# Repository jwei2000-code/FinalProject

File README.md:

# FinalProject
# The "Deep Work Halo"

## 1. Overview
The Deep Work Halo is a privacy-focused workspace monitor designed to help users maintain and signal a "Flow State" without distraction. It consists of a discreet wearable that analyzes head stability to detect focus levels and wirelessly updates a desktop analog gauge. This gauge visually communicates the user's cognitive state to colleagues, acting as an automatic "Do Not Disturb" signal when deep work is achieved.

## 2. Visual Concept & Physical Design

### The Sensing Device (The "Smart Ear-Cuff")
* **Form Factor:** It uses a C-bridge design. One part sits behind the ear (battery/logic), and a smaller part sits inside/front of the ear (sensor), connected by a flexible silicone bridge.
* **Physical Features:** Completely screen-less and light-less to prevent user distraction. It houses the internal electronics and battery, featuring only a single pinhole reset button on the back.

### The Display Device ("The Flow Monolith")
* **Form Factor:** A minimalist, solid cube or rectangular prism (approx. 6cm x 6cm).
* **Materials:**
    * **Inner Core:** Matte black internal chassis.
    * **Outer Shell:** Thick, frosted clear acrylic (or smoked polycarbonate) acting as a massive light diffuser.
* **The Interface (Visual):**
    * **Screen:** A hidden LED Dot Matrix (8x8 or 16x16 grids) or a low-res OLED behind the acrylic face.
    * **Typography:** Uses a strict **Bitmap / Pixel font** for a retro-futuristic aesthetic.
    * **Function:** Displays the current time by default. When focus is detected, it transitions to a "Focus Score" (0-100) or a pixelated status icon.
* **The Interface (Atmosphere):**
    * **Breathing Light:** Buried RGB LEDs illuminate the entire acrylic block from within.
    * **Behavior:**
        * *Standby:* Off or faint white (Clock Mode).
        * *Flow State:* Gently pulses in warm Amber/Red (Do Not Disturb signal).

## 3. Technical Architecture

### Sensors & Inputs (The "Sense")
* **Device:** 6-Axis IMU (Inertial Measurement Unit).
* **Function:** Captures accelerometer and gyroscope data to track head micro-movements.
* **Logic:** A TinyML model running locally on the wearable classifies data into states (e.g., Focused vs. Fidgeting vs. Talking).

### Interface & Outputs (The "Feedback")
* **Stepper Motor:** Provides non-intrusive, peripheral visual feedback on focus depth.
* **RGB LED Ring:** Provides social signaling (Red/Amber = DND) to the external environment.

### Connectivity & Power
* **Wireless Protocol:** BLE (Bluetooth Low Energy) for efficient communication between the Wearable (Server) and Desktop Gauge (Client).
* **Power Source:**
    * *Wearable:* CR2032 Coin Cell (optimized for deep sleep).
    * *Desktop:* LiPo battery with USB-C charging.

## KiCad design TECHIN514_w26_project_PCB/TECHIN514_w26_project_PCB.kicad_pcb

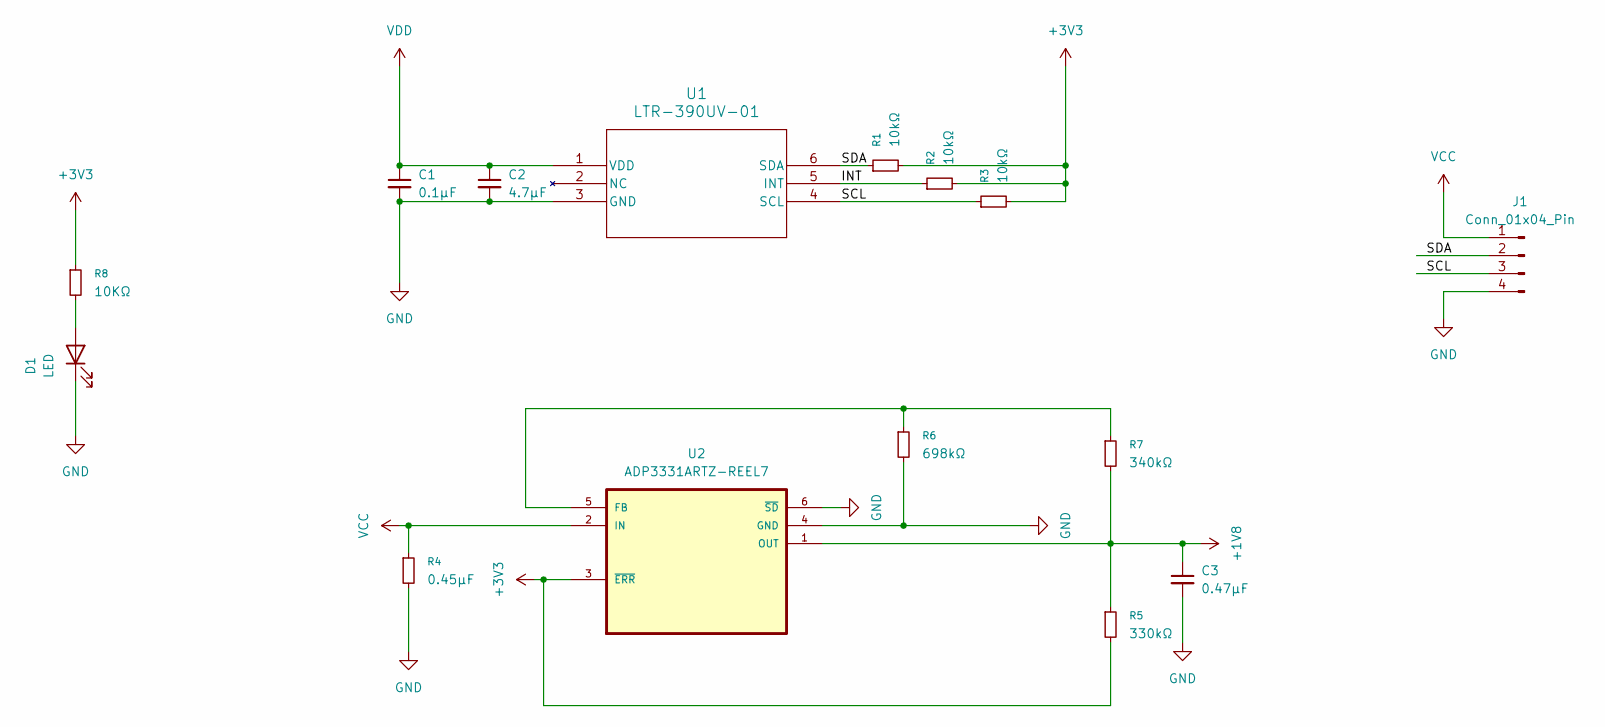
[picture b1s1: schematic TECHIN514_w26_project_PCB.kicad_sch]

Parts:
C1: 0.1µF; C_0603_1608Metric_Pad1.08x0.95mm_HandSolder
C2: 4.7µF; C_0603_1608Metric_Pad1.08x0.95mm_HandSolder
C3: 0.47µF; C_0603_1608Metric_Pad1.08x0.95mm_HandSolder
D1: LED; LED_0603_1608Metric_Pad1.05x0.95mm_HandSolder
J1: Conn_01x04_Pin; PinSocket_1x04_P2.54mm_Vertical
R1, R2, R3: 10kΩ; R_0603_1608Metric_Pad0.98x0.95mm_HandSolder
R4: 0.45µF; R_0603_1608Metric_Pad0.98x0.95mm_HandSolder
R5: 330kΩ; R_0603_1608Metric_Pad0.98x0.95mm_HandSolder
R6: 698kΩ; R_0603_1608Metric_Pad0.98x0.95mm_HandSolder
R7: 340kΩ; R_0603_1608Metric_Pad0.98x0.95mm_HandSolder
R8: 10KΩ; R_0603_1608Metric_Pad0.98x0.95mm_HandSolder
U1: LTR-390UV-01; SMD6_LTR-390UV-01_LTO
U2: ADP3331ARTZ-REEL7; SOT95P280X145-6N

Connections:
+1V8: C3.1, R5.1, R7.2, U2.1 (OUT)
+3V3: R1.2, R2.2, R3.2, R5.2, R8.1, U2.3 (~ERR)
/INT: R2.1, U1.5 (INT)
/SCL: J1.3, R3.1, U1.4 (SCL)
/SDA: J1.2, R1.1, U1.6 (SDA)
GND: C1.2, C2.2, C3.2, D1.1 (K), J1.4, R4.2, R6.2, U1.3 (GND), U2.4 (GND), U2.6 (~SD)
unnamed: D1.2 (A), R8.2
unnamed: R6.1, R7.1, U2.5 (FB)
VCC: J1.1, R4.1, U2.2 (IN)
VDD: C1.1, C2.1, U1.1 (VDD)

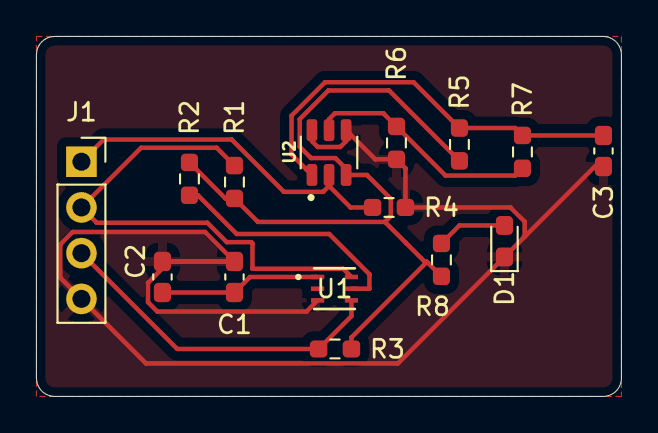
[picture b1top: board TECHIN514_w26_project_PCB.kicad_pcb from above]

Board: 2 copper layers, 32.5 x 20.0 mm, 15 parts (0 on the bottom side), 10 nets.

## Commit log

2026-01-20 second
2026-01-20 third
2026-01-20 pictures
2026-01-20 sheets
2026-01-30 Initial upload of project folder
